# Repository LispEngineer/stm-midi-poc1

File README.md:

# MIDI Synthesizer Proof of Concept 1

**Feedback is very welcome!**

* Author: [Douglas P. Fields, Jr.](mailto:symbolics@lisp.engineer)
* My portions Copyright 2024 Douglas P. Fields, Jr.
* My portions License: Creative Commons Attribution-ShareAlike 4.0
  * AKA `CC BY-SA 4.0`
  * [See LICENSE.md](LICENSE.md) or [CC site](https://creativecommons.org/licenses/by-sa/4.0/deed.en)
* Started 2024-09-28
* Last updated 2025-04-20
* [Repo Self-Link](https://github.com/LispEngineer/stm-midi-poc1)

Overviews:
* 3D Views
  * 
  * 
* [Schematic PDF](stm-midi-poc1.pdf)
* [Board Plots as PDF](plots/stm-midi-poc1__Assembly.pdf)
  * From Board2PDF KiCAD Plugin
* [Interactive BOM](bom/ibom.html)
  * From Interactive BOM KiCAD Plugin

Design documents:
* [Design notes](Design.md)
* Designed in [KiCAD 8](https://www.kicad.org/)
* LCSC part numbers included for assembly by [JLCPCB](https://jlcpcb.com/)

Debuggers:
* Segger J-Link EDU Mini
* Segger J-Link Plus v10.1 (second hand)
  * Built in VCOM port - only seems to work at 115,200 baud
* ST-Link v3
* FTDI USB to TTL UART

Software:
* [Pinout](https://github.com/LispEngineer/stm-midi-poc1-sw)
* [STM Synth](https://github.com/LispEngineer/nucleo-uart)
* [My KiCAD Libraries](https://github.com/LispEngineer/KiCAD_Libraries)

Discussions:
* [Smaller Optoisolator](https://www.reddit.com/r/synthdiy/comments/1gghujj/smaller_midi_optoisolator/)

## Key Reference Documents

* [DS11853](TODO) - Datasheet: Arm® Cortex®-M7 32b MCU+FPU, 462DMIPS, up to 512KB Flash
  256+16+4KB RAM, USB OTG HS/FS, 18 TIMs, 3 ADCs, 21 com IF
* [RM0431](TODO) - STM32F72xxx ... advanced Arm®-based 32-bit MCUs
* [PM0253](TODO) - STM32F7 Series ... Cortex®-M7 processor programming manual
* [ES0360](TODO) - STM32F72xxx ... device limitations
* [AN2867](TODO) - Guidelines for oscillator design on ... STM32 MCUs/MPUs
* [AN4661](TODO) - Getting started with STM32F7 Series MCU hardware development
* [AN5612](TODO) - ESD protection of STM32 MCUs
* [AN4879](TODO) - Introduction to USB hardware and PCB guidelines using STM32 MCUs
* [AN4989](TODO) - STM32 microcontroller debug toolbox
* [AN4676](TODO) - STM32F7 Series peripheral interconnections
* [AN4031](TODO) - Using the STM32F2, STM32F4 and STM32F7 Series DMA controller

Moving to STM32H7:
* [AN5293](TODO) - Migration guide from STM32F7 Series to STMH74x/75x, STM32H72x/73x and STMH7A3/7Bx devices
* [AN4936](TODO) - Migration of microcontroller applications from STM32F7 Series to STM32H743/753 line

# Production Runs

I have been using JLCPCB.

* [JLCPCB instructions](https://jlcpcb.com/help/article/how-to-generate-gerber-and-drill-files-in-kicad-8)
  on creating Gerber and Drill files for KiCAD 8.
* You can also use the
  [JLCPCB KiCAD plugin](https://github.com/Bouni/kicad-jlcpcb-tools).
  * Installed using the *Plugin and Content Manager* in KiCAD.
  * This usefully shows you the stock count for your parts, and whether
    they are Basic or Extended.
  * Current version (2024-12-21) gives a lot of errors about redundant
    parts already in the catalog though (annoying).
* Or maybe I was using [this JLCPCB KiCAD plugin](https://github.com/bennymeg/Fabrication-Toolkit).

## Run 1 - EVT#1

* Submitted: 2024-10-27
* Git Commit: `6f9e281abe9c22ef3b995376c3df42217fc04524`
* Producer: JLCPCB
  * Order #W202410271206812 
* Boards: 5
* Assemblies: 2
* [BOM](jlcpcb/production_files/BOM-stm-midi-poc1.csv)
* [CPL](jlcpcb/production_files/CPL-stm-midi-poc1.csv)
* [Gerbers](jlcpcb/production_files/GERBER-stm-midi-poc1.zip)
* JLCPCB Corrected Part Placement
  
* [JLCPCB Submission](jlcpcb-production/run1-20241027/stm-midi-poc1 6f9e281abe9c22ef3b995376c3df42217fc04524_Y2.zip)
* Status: Production complete; in DHL's hands for delivery Nov 8
* Cost:
  * PCB: $28.02
  * Assembly: $79.66
  * Shipping: $32.60 (DHL)
  * Sales tax: $11.22
  * Total: $151.50

I received two fully populated boards. One was missing the J5 header.

## Run 2 - EVT#2

* Submitted: 2024-12-21 (11PM NYC time)
  * PCB and PCBA confirmed: 2024-12-22
* Git Commit: `e48a22093a1c81bb14c9082240e3d44837e7d75e`
* Producer: JLCPCB
* Order #W202412221204947 
* Boards: 5
* Assemblies: 2
* [BOM](jlcpcb/production_files/BOM-stm-midi-poc1.csv)
* [CPL](jlcpcb/production_files/CPL-stm-midi-poc1.csv)
* [Gerbers](jlcpcb/production_files/GERBER-stm-midi-poc1.zip)
* JLCPCB Corrected Part Placement
  
* [JLCPCB Submission](jlcpcb-production/run2-20241221/GERBER-stm-midi-poc1_Y3.zip)
* Status: Confirmed for PCB/PCBA
* Cost:
  * PCB: $8.00
  * Assembly: $86.40
  * Shipping: $58.36 (FedEx - "remote area" charge)
  * Sales tax: $12.22
  * Total: $164.98
* Received: 2025-01-03 (delivered on 2025-01-02)

Results:
* They did not add assembly holes this time (interesting, maybe re-used the mounting holes)
* STM32 Debugger (ST-Link v3) does not seem to reliably connect anymore.
  * It did allow me to download the firmware but is not reliable.
  * Sometimes it says "Failed to enable Live Expressions"
* SPI display works
* Audio Gain pins work
* Audio mute works
* Headphone output works
* Buttons & LEDs work

TODO:
* Test MIDI in/out
* Test Line out
* Test various resistors for the headphone
* Test I2C
* Test GPIO

# Miscellaneous Notes

* Footprints, models, etc., by their respective authors
* Some footprints, schematics, models are from these sources:
  * [Component Search Engine](https://componentsearchengine.com)
  * [Snap EDA](https://snapeda.com)
  * [EasyEDA](https://easyeda.com)
* Useful tools:
  * [EasyEDA2KiCAD](https://github.com/uPesy/easyeda2kicad.py)
  * [JLC Parts Finder](https://yaqwsx.github.io/jlcparts/)
  * [Altium Viewer](https://www.altium365.com/viewer/)
    * If you have Altium files and want to get details out of them
      but only use KiCAD

# KiCAD Configuration Notes

Using EasyEDA2KiCAD:

* Create a Path Substitution
  * Use main KiCAD window: Prefernces -> Configure Paths...
  * `EASYEDA2KICAD`
  * [Git Repository](https://github.com/LispEngineer/KiCAD_Libraries)
* Create a Footprint Library
  * `easyeda2kicad` Nickname
  * `${EASYEDA2KICAD}/easyeda2kicad.pretty`
* Create a Symbol Library
  * `easyeda2kicad` Nickname
  * `${EASYEDA2KICAD}/easyeda2kicad.kicad_sym` Library Path

# Status

* Schematic: Done
* LCSC part IDs: Almost Done
  * Need non-Red LEDs
* Schematic symbols: Done
* Footprints: Done
* 3D models: Done
* PCB Layout: Done
* Production 1 run: Done - in shipping

## TODOs

* Use STDC14 connector for ST-Link v3
  * Digikey [1175-1632-ND](https://www.digikey.com/en/products/detail/cnc-tech/3220-14-0300-00/3883270?s=N4IgTCBcDaIIxwOwFYC0cBsBmMqByAIgAQgC6AvkA)
    * Not in JLCPCB
  * Mouser [SHF-107-01-L-D-SM](https://www.mouser.com/ProductDetail/Samtec/SHF-107-01-L-D-SM?qs=%252BZP6%2F%252BtExtBY5XT826bN4g%3D%3D)
    * [Footprint](https://kinetictest.samtec.com/partnumber/shf-107-01-l-d-sm#featureinformation)
    * [JLCPCB C17640678](https://jlcpcb.com/partdetail/Samtec-SHF_107_01_L_DSM/C17640678) - $2???
    * [LCSC Alternative 1](https://www.lcsc.com/product-detail/Pin-Headers_Hanbo-Electronic-Hanbo-Electronic-HB-PH9-12727PB2GOB_C6332251.html) C6332251
    * [LCSC Alternative 2](https://www.lcsc.com/product-detail/Pin-Headers_HCTL-HCTL-PZ127-2-07-S_C3975190.html) C3975190 - 11¢
    * [LCSC Alternative 3](https://www.lcsc.com/product-detail/Pin-Headers_XKB-Connection-XKB-Connection-X1321WVS-2x07J-C40D53_C2881912.html) C2881912
* Use a 4-pin 32kHz clock?
* RN1 footprint and 3D model look a little bit off - footprint is a bit too small?
* Test points/pins
* MCU Pin 24 is not used - it is I2S1_MCK
* Incorporate my own ST-Link?
  * [See Hackaday](https://hackaday.io/project/179054-custom-st-link-v20-v21-v30)

### DONE

* DONE(EVT2): Find a much smaller Opto-isolator for MIDI than the one chosen here
  * [TLP2362](https://toshiba.semicon-storage.com/us/semiconductor/product/isolators-solid-state-relays/detail.TLP2362.html)
    is used by [Ksoloti 0.6](https://ksoloti.github.io/5-resources.html). Tested to work with
    1.8kΩ pull-up resistor instead of the schematic's 2.7kΩ.
    (Also worked with no pull-up resistor!)

# Board Layout Notes

4-layer design with Signal/GND/GND/Signal for EVT board.

Will do most important routing first on the top copper layer:
* Decoupling/bypass capacitors
* Clock signals
* High speed signals
  * USB
  * DAC
  * SWD

Remaining signals will be routed using "Manhattan routing."
That is, one signal layer will run up/down, the other will
run left/right, mostly.
* Top layer: up/down
* Bottom layer: left/right

After that, do these routings:
* Audio signals
* MIDI signals
* SPI
* I²C
* UI (Buttons, LEDs)
* GPIO
* Power

Fill in some positive power areas with fill.

Finally, the signal layers will be filled with GND at the end,
and the ground planes should be stitched together with lots
of vias.

## After Layout Is Done

* DRC check
* Cleanup Tracks & Vias

# BOM Notes

* Docs say you need a 4.7 uF ceramic capacitor with low ESR DS11853 Rev 9 page 105
  * Samsung CL10A475KO8NNNC works *but* Datasheet doesn't say what the ESR is, just "low ESR"
  * [Notes on the Cap](https://community.st.com/t5/stm32-mcus-products/how-supply-stm32f446ret6/td-p/635424)

* [ISOM8710](https://www.ti.com/product/ISOM8710) 
  is a drop-in replacement for the
  [TLP2362](https://toshiba.semicon-storage.com/us/semiconductor/product/isolators-solid-state-relays/detail.TLP2362.html)
  * Same form factor
  * Same functionality (tested on a breadboard)
  * Same circuit
  * Does not seem to be carried at JLCPCB

# Notes for future

* Use fewer header types, they're all extended parts
* Don't use the Resistor Network - due to the Extended parts fee from JLC
  * OTOH there are no 56Ω resistors in the Basic parts library
  * C25127 is an extended part 0402
  * C17714 is an 0805 47Ω
* Add I/O activity LEDs for MIDI & serial?
* Add a pin for VBUS (5V from USB) and USB GND
* Add pins for the TRS jacks
* Get a 4-way switch for gain?
* Rewrire the headphone amp like Pimoroni?
* Move console from UART3 to UART2
  * Move console pins next to SWD pins for easy use with STLink
* Install UART to USB bridge
  * [FTDI FT234XD](https://ftdichip.com/products/ft234xd/) is a nice 12-pin package
  * [Example Circuit](https://github.com/z4yx/USB-C-Serial)
  * [JLCPCB Part](https://jlcpcb.com/partdetail/Ftdi-FT234XDR/C132158)

Longer term
* Move to an STM32H7 device
* Move to a [higher pin-count device](https://www.st.com/en/microcontrollers-microprocessors/stm32h7-series/products.html)
  * LQFP 64, 100, 144, 176, 208
    * low-profile quad flat package - LQFP 64 currently in use
  * TFBGA 216, 225, 240+25
    * Thin Profile Fine Pitch Ball Grid Array
    * thinner than other BGA packages - Gemini
  * UFBGA 144, 169, 176+25
    * ultra fine pitch ball grid array
  * VFQFPN 68
    * thermally enhanced very thin profile fine pitch quad flat package no lead (Gemini)
  * WLCSP 132, 156
    * [Wafer-Level Chip Scale Packaging](https://www.flashpcb.com/blog/QFP-QFN-BGA-WLSCP)
* Add an SDRAM

# EasyEDA 2 KiCAD Notes

`python -m easyeda2kicad --full --lcsc_id=Cxxxxx`

[My imported library is in GitHub](https://github.com/LispEngineer/KiCAD_Libraries).

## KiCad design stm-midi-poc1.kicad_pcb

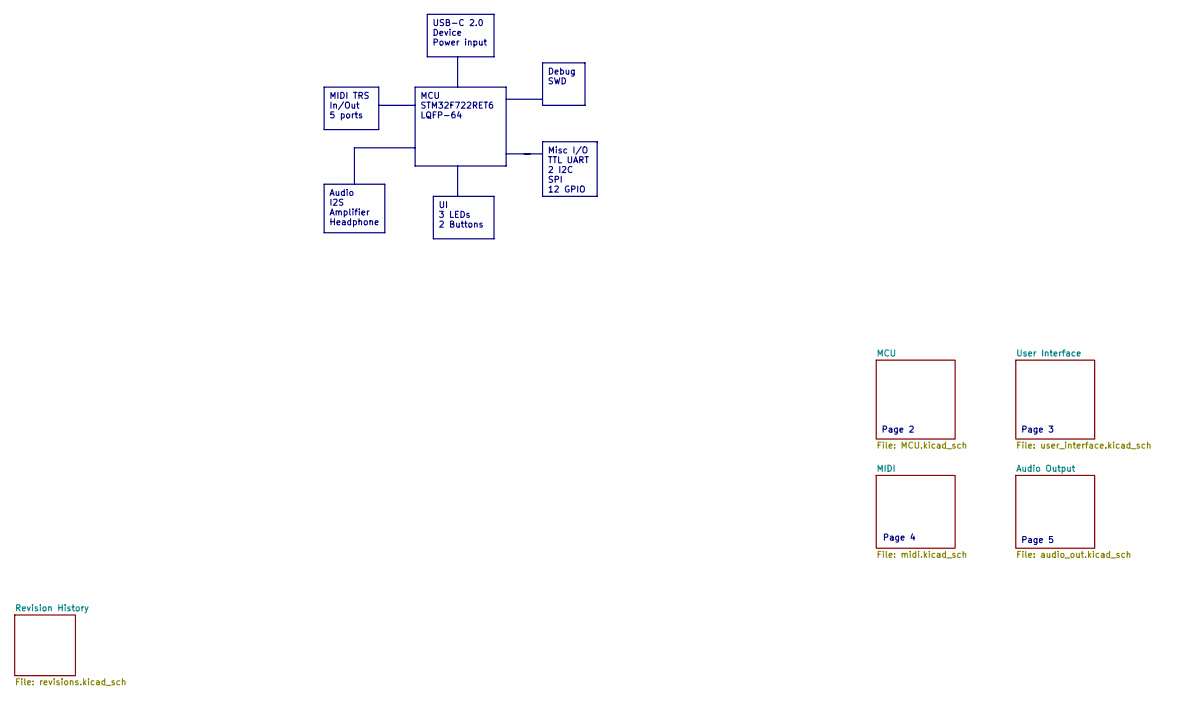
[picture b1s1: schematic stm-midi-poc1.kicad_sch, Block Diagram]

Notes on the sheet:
MIDI TRS In/Out 5 ports
Misc I/O TTL UART 2 I2C SPI 12 GPIO
MCU STM32F722RET6 LQFP-64
UI 3 LEDs 2 Buttons
USB-C 2.0 Device Power input
Audio I2S Amplifier Headphone
Debug SWD
Page 5
Page 3
Page 2
Page 4

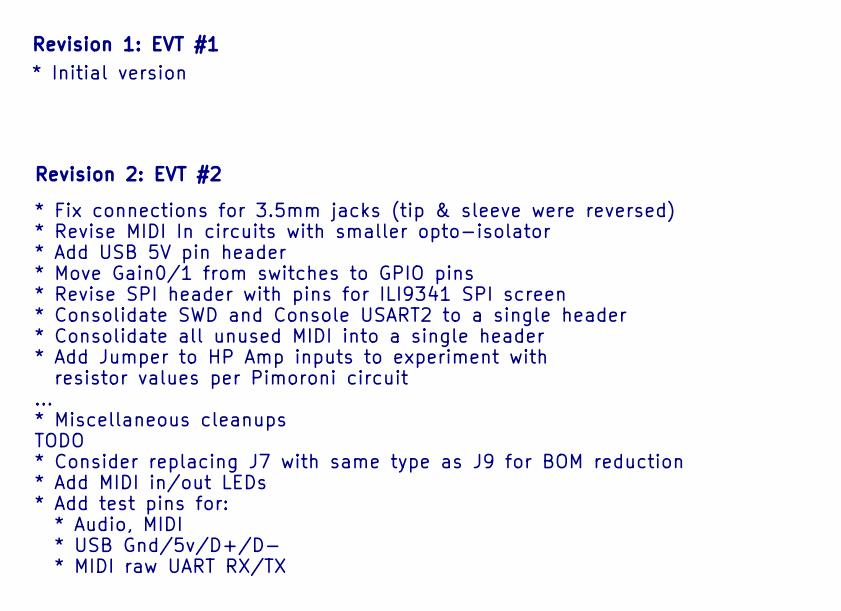
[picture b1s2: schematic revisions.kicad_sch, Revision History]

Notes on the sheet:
Revision 1: EVT #1
* Fix connections for 3.5mm jacks (tip & sleeve were reversed) * Revise MIDI In circuits with smaller opto-isolator * Add USB 5V pin header * Move Gain0/1 from switches to GPIO pins * Revise SPI header with pins for ILI9341 SPI screen * Consolidate SWD and Console USART2 to a single header * Consol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
Revision 2: EVT #2
* Initial version

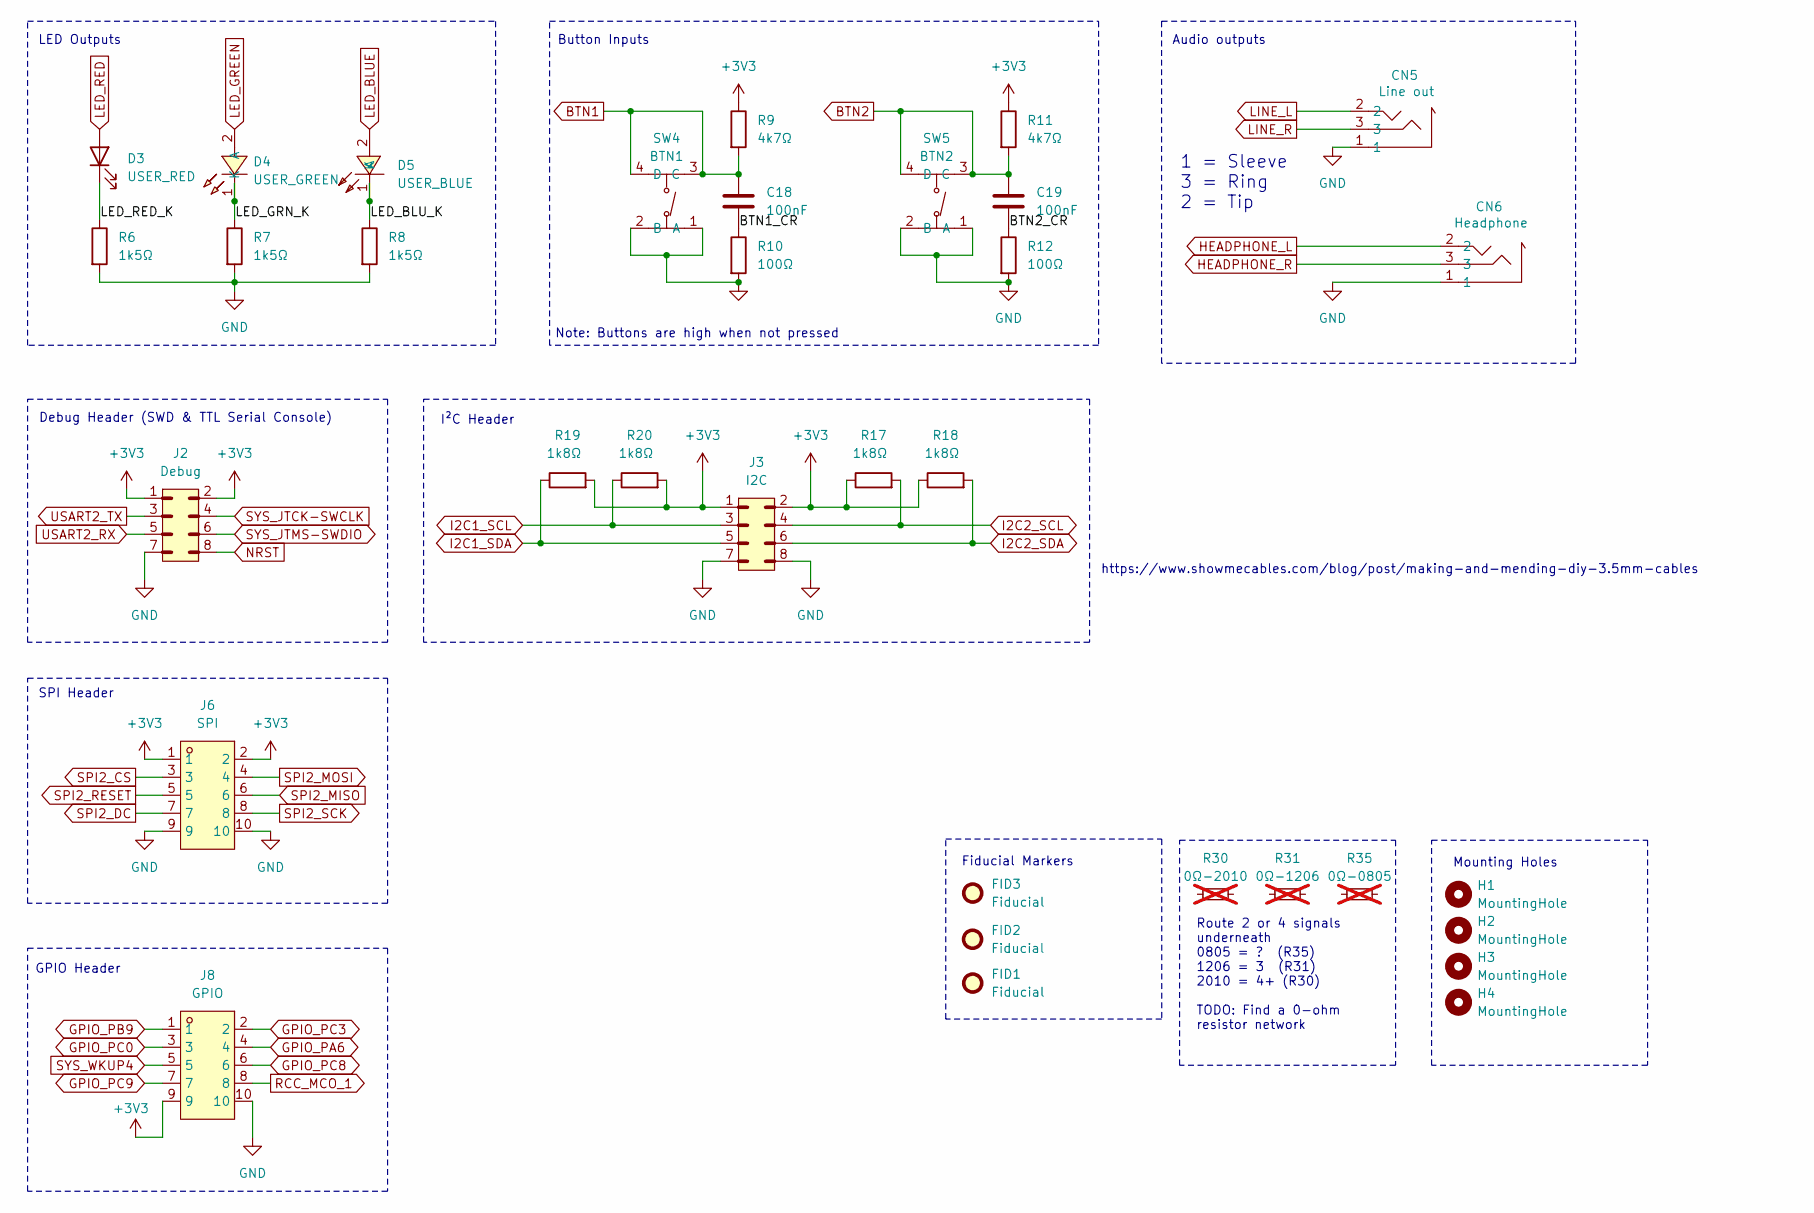
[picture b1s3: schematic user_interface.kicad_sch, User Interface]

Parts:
C18, C19: 100nF; C_0402_1005Metric; Manu Part CL05B104KB54PNC; LCSC C307331
CN5: Line out; AUDIO-SMD_PJ-321A-4A; Manu Part PJ-321A-4A; LCSC Part C879743
CN6: Headphone; AUDIO-SMD_PJ-321A-4A; Manu Part PJ-321A-4A; LCSC Part C879743
D3: USER_RED; LED_0603_1608Metric; Manu Part KT-0603R; LCSC C2286
D4: USER_GREEN; LED0603-RD; LCSC Part C19189745
D5: USER_BLUE; LED0603-RD; LCSC Part C2288
FID1, FID2, FID3: Fiducial; Fiducial_1mm_Mask2mm
H1, H2, H3, H4: MountingHole; MountingHole_2.2mm_M2
J2: Debug; PinHeader_2x04_P2.54mm_Vertical; Manu Part PZ2.54-2*4; LCSC C5156676
J3: I2C; PinHeader_2x04_P2.54mm_Vertical; Manu Part PZ2.54-2*4; LCSC C5156676
J6: SPI; HDR-TH_10P-P2.54-V-M-R2-C5-S2.54-1; LCSC Part C5156677
J8: GPIO; HDR-TH_10P-P2.54-V-M-R2-C5-S2.54-1; LCSC Part C5156677
R6, R7, R8: 1k5Ω; R_0402_1005Metric; Manu Part 0402WGF1501TCE; LCSC C25867
R9, R11: 4k7Ω; R_0402_1005Metric; Manu Part 0402WGF4701TCE; LCSC C25900
R10, R12: 100Ω; R_0402_1005Metric; Manu Part 0402WGF1000TCE; LCSC C25076
R17, R18, R19, R20: 1k8Ω; R_0402_1005Metric; Manu Part 0402WGF1801TCE; LCSC C25871
R30: 0Ω-2010; R_2010_5025Metric; Manu Part AC2010JK-070RL; LCSC C144433; not fitted
R31: 0Ω-1206; R_1206_3216Metric; Manu Part 1206W4F0000T5E; LCSC C17888; not fitted
R35: 0Ω-0805; R_0805_2012Metric; Manu Part 0805W8F0000T5E; LCSC C17477; not fitted
SW4: BTN1; SW-SMD_4P-L5.1-W5.1-P3.70-LS6.5-TL-2; Manu Part TS-1187A-B-A-B; LCSC Part C318884
SW5: BTN2; SW-SMD_4P-L5.1-W5.1-P3.70-LS6.5-TL-2; Manu Part TS-1187A-B-A-B; LCSC Part C318884

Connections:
+3V3: J2.1, J2.2, J3.1, J3.2, J6.1, J6.2, J8.9, R9.1, R11.1, R17.1, R18.1, R19.2, R20.2; also elsewhere on the board
/User Interface/BTN1_CR: C18.2, R10.1
/User Interface/BTN2_CR: C19.2, R12.1
/User Interface/LED_BLU_K: D5.1 (K), R8.1
/User Interface/LED_GRN_K: D4.1 (K), R7.1
/User Interface/LED_RED_K: D3.1 (K), R6.1
BTN1: C18.1, R9.2, SW4.3 (C), SW4.4 (D); also elsewhere on the board
BTN2: C19.1, R11.2, SW5.3 (C), SW5.4 (D); also elsewhere on the board
GND: CN5.1, CN6.1, J2.7, J3.7, J3.8, J6.9, J6.10, J8.10, R6.2, R7.2, R8.2, R10.2, R12.2, SW4.1 (A), SW4.2 (B), SW5.1 (A), SW5.2 (B); also elsewhere on the board
GPIO_PA6: J8.4; also elsewhere on the board
GPIO_PB9: J8.1; also elsewhere on the board
GPIO_PC0: J8.3; also elsewhere on the board
GPIO_PC3: J8.2; also elsewhere on the board
GPIO_PC8: J8.6; also elsewhere on the board
GPIO_PC9: J8.7; also elsewhere on the board
HEADPHONE_L: CN6.2; also elsewhere on the board
HEADPHONE_R: CN6.3; also elsewhere on the board
I2C1_SCL: J3.3, R20.1; also elsewhere on the board
I2C1_SDA: J3.5, R19.1; also elsewhere on the board
I2C2_SCL: J3.4, R17.2; also elsewhere on the board
I2C2_SDA: J3.6, R18.2; also elsewhere on the board
LED_BLUE: D5.2 (A); also elsewhere on the board
LED_GREEN: D4.2 (A); also elsewhere on the board
LED_RED: D3.2 (A); also elsewhere on the board
LINE_L: CN5.2; also elsewhere on the board
LINE_R: CN5.3; also elsewhere on the board
NRST: J2.8; also elsewhere on the board
RCC_MCO_1: J8.8; also elsewhere on the board
SPI2_CS: J6.3; also elsewhere on the board
SPI2_DC: J6.7; also elsewhere on the board
SPI2_MISO: J6.6; also elsewhere on the board
SPI2_MOSI: J6.4; also elsewhere on the board
SPI2_RESET: J6.5; also elsewhere on the board
SPI2_SCK: J6.8; also elsewhere on the board
SYS_JTCK-SWCLK: J2.4; also elsewhere on the board
SYS_JTMS-SWDIO: J2.6; also elsewhere on the board
SYS_WKUP4: J8.5; also elsewhere on the board
USART2_RX: J2.5; also elsewhere on the board
USART2_TX: J2.3; also elsewhere on the board

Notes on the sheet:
Mounting Holes
SPI Header
Debug Header (SWD & TTL Serial Console)
1 = Sleeve 3 = Ring 2 = Tip
Note: Buttons are high when not pressed
Route 2 or 4 signals underneath 0805 = ? (R35) 1206 = 3 (R31) 2010 = 4+ (R30) TODO: Find a 0-ohm resistor network
Audio outputs
GPIO Header
I²C Header
LED Outputs
https://www.showmecables.com/blog/post/making-and-mending-diy-3.5mm-cables
Button Inputs
Fiducial Markers

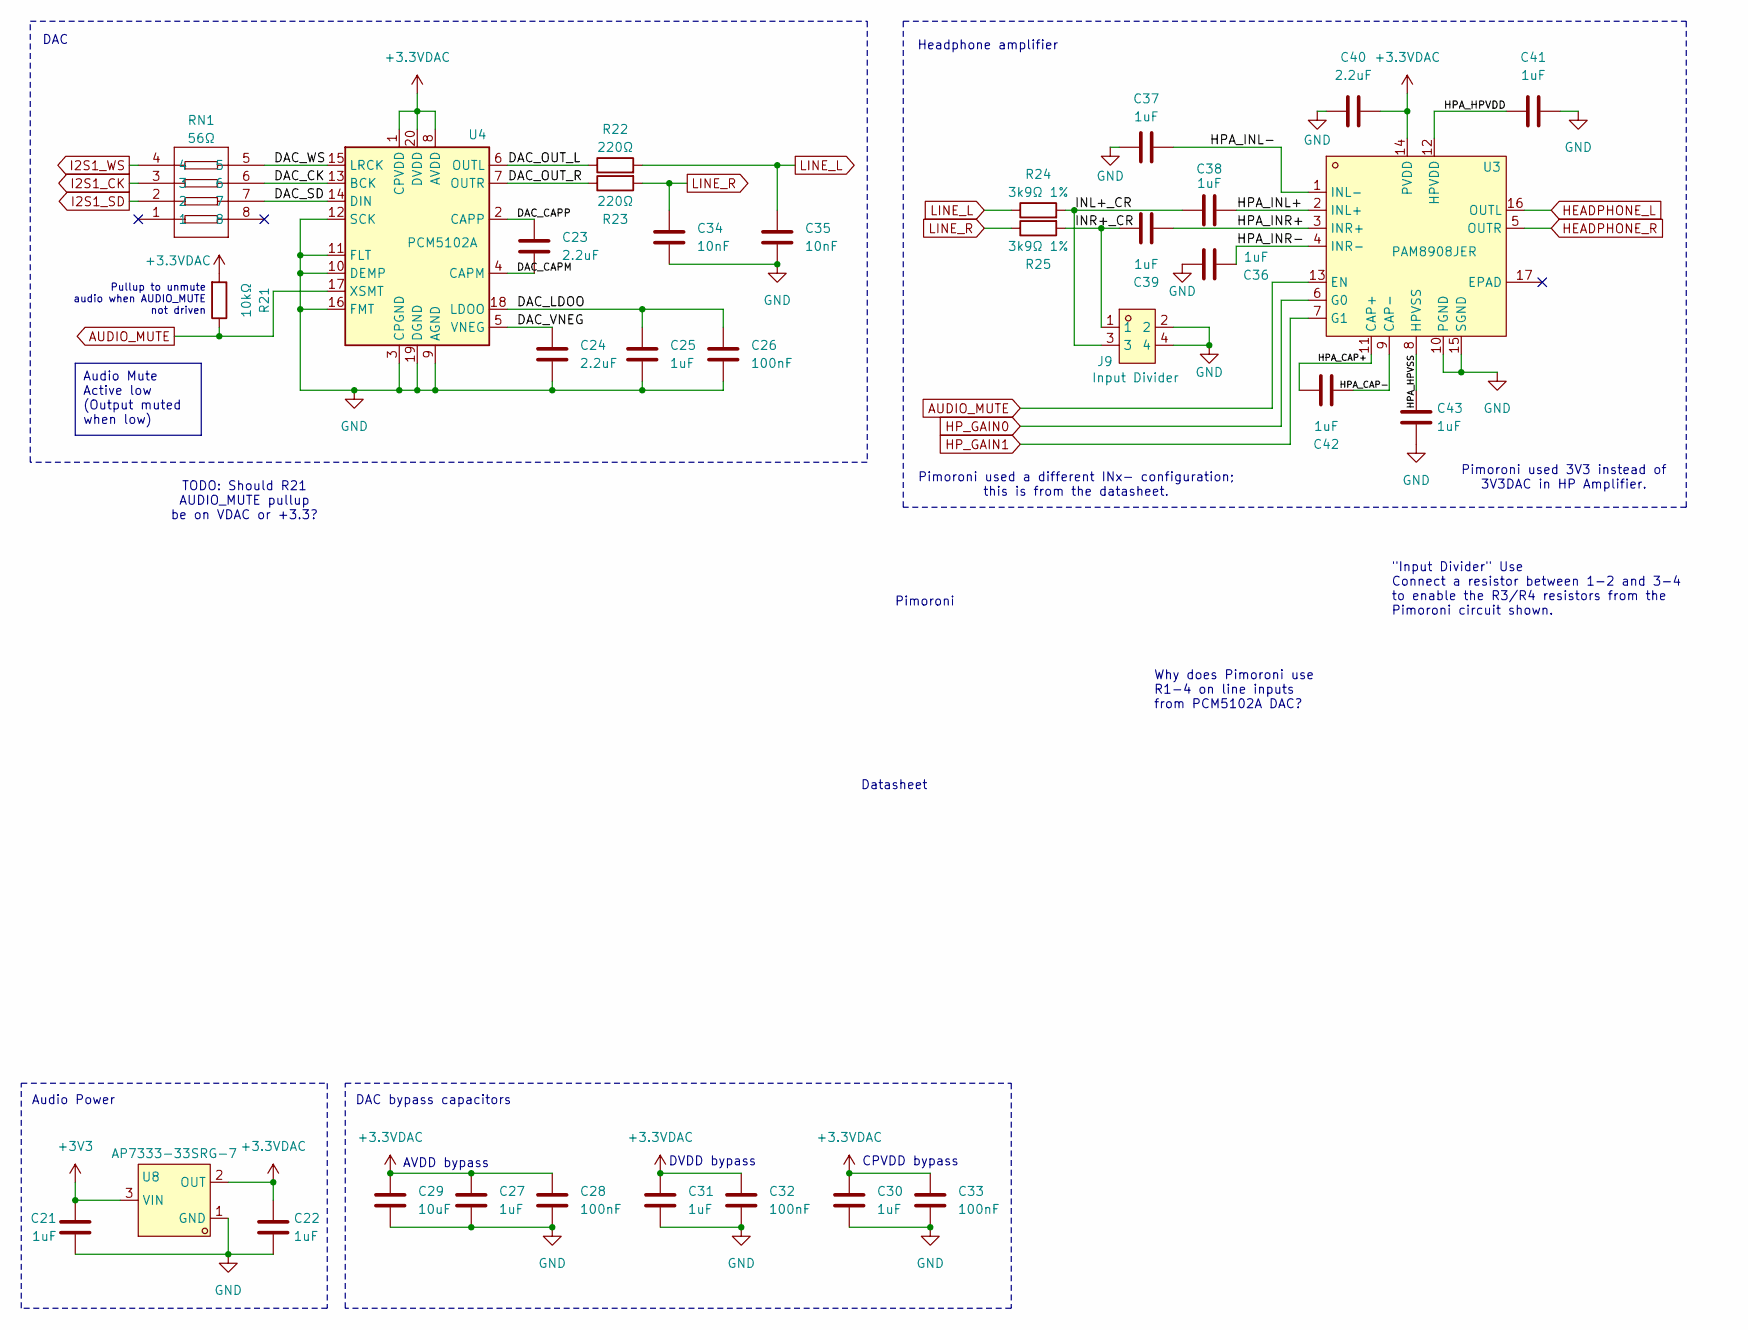
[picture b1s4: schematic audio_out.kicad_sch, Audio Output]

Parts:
C21, C22, C25, C27, C30, C31, C36, C37, C38, C39, C41, C42, C43: 1uF; C_0402_1005Metric; Manu Part CL05A105KA5NQNC; LCSC C52923
C23, C24, C40: 2.2uF; C_0805_2012Metric; Manu Part CL21A225KBQNNNE; LCSC C377773
C26, C28, C32, C33: 100nF; C_0402_1005Metric; Manu Part CL05B104KB54PNC; LCSC C307331
C29: 10uF; C_0603_1608Metric; Manu Part CL10A106MA8NRNC; LCSC C96446
C34, C35: 10nF; C_0402_1005Metric; Manu Part CL05B103KB5NNNC; LCSC C15195
J9: Input Divider; HDR-TH_4P-P2.54-V-F-R2-C2-S2.54; LCSC Part C2977590
R21: 10kΩ; R_0402_1005Metric; Manu Part 0402WGF1002TCE; LCSC C25744
R22, R23: 220Ω; R_0402_1005Metric; Manu Part 0402WGF2200TCE; LCSC C25091
R24, R25: 3k9Ω 1%; R_0402_1005Metric; Manu Part 0402WGF3901TCE; LCSC C51721
RN1: 56Ω; RES-ARRAY-SMD_0603-8P-L3.2-W1.6-BL; Manu Part 4D03WGJ0560T5E; LCSC Part C25512
U3: PAM8908JER; QFN-16_L3.0-W3.0-P0.50-BL-EP1.7; Manu Part PAM8908JER; LCSC Part C33233
U4: PCM5102A; TSSOP-20_4.4x6.5mm_P0.65mm; Manu Part PCM5102APWR; LCSC C107671
U8: AP7333-33SRG-7; SOT-23-3_L2.9-W1.3-P1.90-LS2.4-BR; Manu Part AP7333-33SRG-7; LCSC Part C150745

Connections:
+3.3VDAC: C22.1, C27.1, C28.1, C29.1, C30.1, C31.1, C32.1, C33.1, C40.2, R21.2, U3.14 (PVDD), U4.1 (CPVDD), U4.8 (AVDD), U4.20 (DVDD), U8.2 (OUT)
+3V3: C21.1, U8.3 (VIN); also elsewhere on the board
/Audio Output/DAC_CAPM: C23.2, U4.4 (CAPM)
/Audio Output/DAC_CAPP: C23.1, U4.2 (CAPP)
/Audio Output/DAC_CK: RN1.6, U4.13 (BCK)
/Audio Output/DAC_LDOO: C25.1, C26.1, U4.18 (LDOO)
/Audio Output/DAC_OUT_L: R22.1, U4.6 (OUTL)
/Audio Output/DAC_OUT_R: R23.1, U4.7 (OUTR)
/Audio Output/DAC_SD: RN1.7, U4.14 (DIN)
/Audio Output/DAC_VNEG: C24.1, U4.5 (VNEG)
/Audio Output/DAC_WS: RN1.5, U4.15 (LRCK)
/Audio Output/HPA_CAP+: C42.2, U3.11 (CAP+)
/Audio Output/HPA_CAP-: C42.1, U3.9 (CAP-)
/Audio Output/HPA_HPVDD: C41.1, U3.12 (HPVDD)
/Audio Output/HPA_HPVSS: C43.1, U3.8 (HPVSS)
/Audio Output/HPA_INL+: C38.2, U3.2 (INL+)
/Audio Output/HPA_INL-: C37.2, U3.1 (INL-)
/Audio Output/HPA_INR+: C39.2, U3.3 (INR+)
/Audio Output/HPA_INR-: C36.2, U3.4 (INR-)
AUDIO_MUTE: R21.1, U3.13 (EN), U4.17 (XSMT); also elsewhere on the board
GND: C21.2, C22.2, C24.2, C25.2, C26.2, C27.2, C28.2, C29.2, C30.2, C31.2, C32.2, C33.2, C34.2, C35.2, C36.1, C37.1, C40.1, C41.2, C43.2, J9.2, J9.4, U3.10 (PGND), U3.15 (SGND), U4.3 (CPGND), U4.9 (AGND), U4.10 (DEMP), U4.11 (FLT), U4.12 (SCK), U4.16 (FMT), U4.19 (DGND), U8.1 (GND); also elsewhere on the board
HEADPHONE_L: U3.16 (OUTL); also elsewhere on the board
HEADPHONE_R: U3.5 (OUTR); also elsewhere on the board
HP_GAIN0: U3.6 (G0); also elsewhere on the board
HP_GAIN1: U3.7 (G1); also elsewhere on the board
I2S1_CK: RN1.3; also elsewhere on the board
I2S1_SD: RN1.2; also elsewhere on the board
I2S1_WS: RN1.4; also elsewhere on the board
LINE_L: C35.1, R22.2, R24.1; also elsewhere on the board
LINE_R: C34.1, R23.2, R25.1; also elsewhere on the board

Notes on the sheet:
Audio Mute Active low (Output muted when low)
Pimoroni used 3V3 instead of 3V3DAC in HP Amplifier.
DVDD bypass
Headphone amplifier
TODO: Should R21 AUDIO_MUTE pullup be on VDAC or +3.3?
Pullup to unmute audio when AUDIO_MUTE not driven
DAC bypass capacitors
CPVDD bypass
Pimoroni
Datasheet
AVDD bypass
Why does Pimoroni use R1-4 on line inputs from PCM5102A DAC?
Audio Power
"Input Divider" Use Connect a resistor between 1-2 and 3-4 to enable the R3/R4 resistors from the Pimoroni circuit shown.
Pimoroni used a different INx- configuration; this is from the datasheet.
DAC

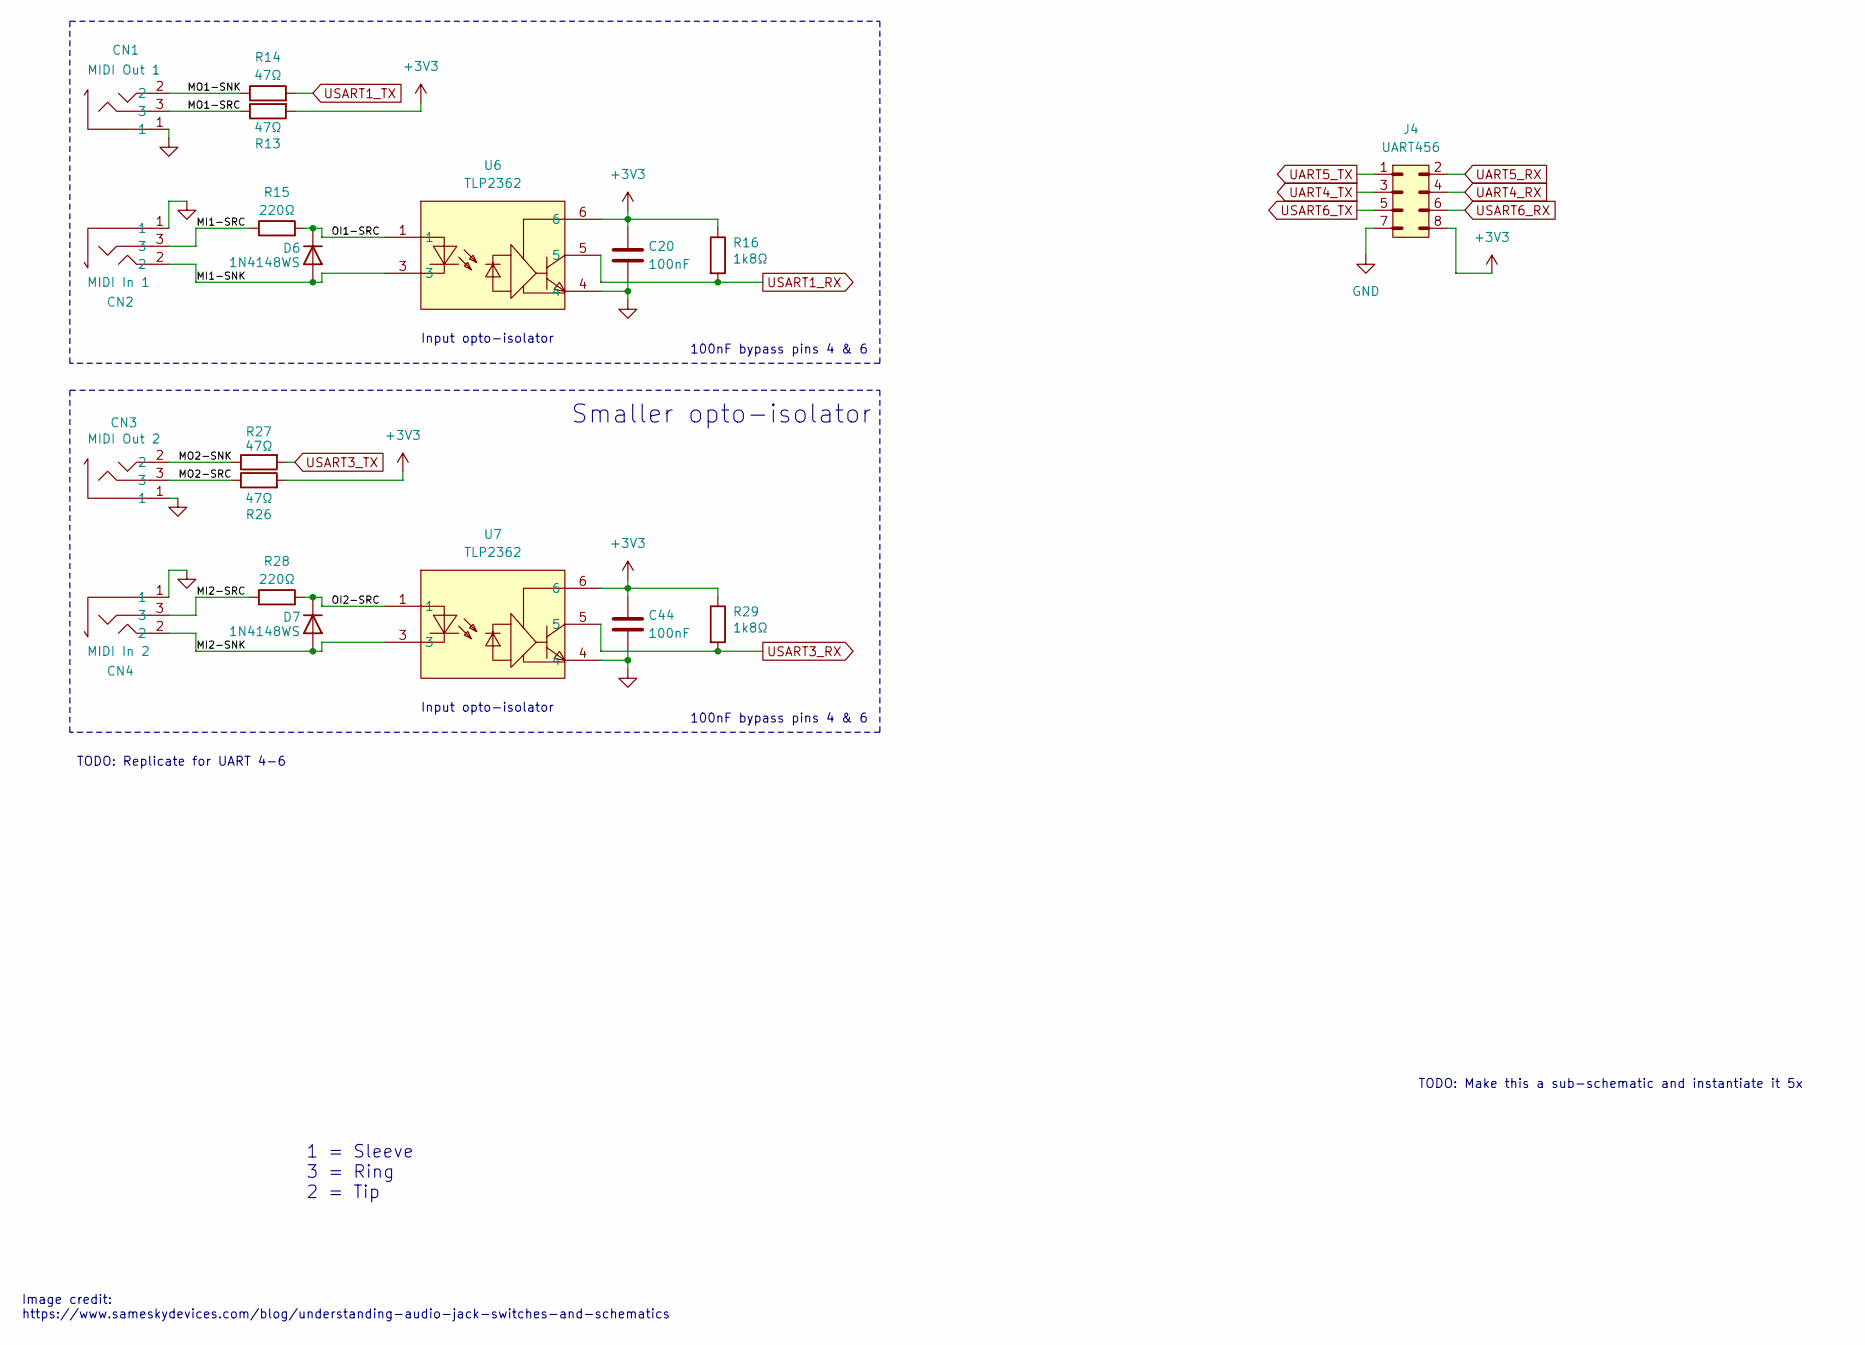
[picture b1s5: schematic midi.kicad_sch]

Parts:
C20, C44: 100nF; C_0402_1005Metric; Manu Part CL05B104KB54PNC; LCSC C307331
CN1: MIDI Out 1; AUDIO-SMD_PJ-321A-4A; Manu Part PJ-321A-4A; LCSC Part C879743
CN2: MIDI In 1; AUDIO-SMD_PJ-321A-4A; Manu Part PJ-321A-4A; LCSC Part C879743
CN3: MIDI Out 2; AUDIO-SMD_PJ-321A-4A; Manu Part PJ-321A-4A; LCSC Part C879743
CN4: MIDI In 2; AUDIO-SMD_PJ-321A-4A; Manu Part PJ-321A-4A; LCSC Part C879743
D6, D7: 1N4148WS; D_SOD-323; LCSC C2128
J4: UART456; PinHeader_2x04_P2.54mm_Vertical; Manu Part PZ2.54-2*4; LCSC C5156676
R13, R14, R26, R27: 47Ω; R_0402_1005Metric; Manu Part 0402WGF470JTCE; LCSC C25118
R15, R28: 220Ω; R_0402_1005Metric; Manu Part 0402WGF2200TCE; LCSC C25091
R16, R29: 1k8Ω; R_0402_1005Metric; Manu Part 0402WGF1801TCE; LCSC C25871
U6, U7: TLP2362; OPTO-SMD-5_L3.7-W4.6-P1.27-LS7.0-BR; LCSC Part C37658

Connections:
+3V3: C20.1, C44.1, J4.8, R13.2, R16.1, R26.2, R29.1, U6.6, U7.6; also elsewhere on the board
/MIDI/MI1-SNK: CN2.2, D6.2 (A), U6.3
/MIDI/MI1-SRC: CN2.3, R15.1
/MIDI/MI2-SNK: CN4.2, D7.2 (A), U7.3
/MIDI/MI2-SRC: CN4.3, R28.1
/MIDI/MO1-SNK: CN1.2, R14.1
/MIDI/MO1-SRC: CN1.3, R13.1
/MIDI/MO2-SNK: CN3.2, R27.1
/MIDI/MO2-SRC: CN3.3, R26.1
/MIDI/OI1-SRC: D6.1 (K), R15.2, U6.1
/MIDI/OI2-SRC: D7.1 (K), R28.2, U7.1
GND: C20.2, C44.2, CN1.1, CN2.1, CN3.1, CN4.1, J4.7, U6.4, U7.4; also elsewhere on the board
UART4_RX: J4.4; also elsewhere on the board
UART4_TX: J4.3; also elsewhere on the board
UART5_RX: J4.2; also elsewhere on the board
UART5_TX: J4.1; also elsewhere on the board
USART1_RX: R16.2, U6.5; also elsewhere on the board
USART1_TX: R14.2; also elsewhere on the board
USART3_RX: R29.2, U7.5; also elsewhere on the board
USART3_TX: R27.2; also elsewhere on the board
USART6_RX: J4.6; also elsewhere on the board
USART6_TX: J4.5; also elsewhere on the board

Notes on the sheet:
Image credit: https://www.sameskydevices.com/blog/understanding-audio-jack-switches-and-schematics
TODO: Replicate for UART 4-6
Input opto-isolator
1 = Sleeve 3 = Ring 2 = Tip
Smaller opto-isolator
TODO: Make this a sub-schematic and instantiate it 5x
100nF bypass pins 4 & 6

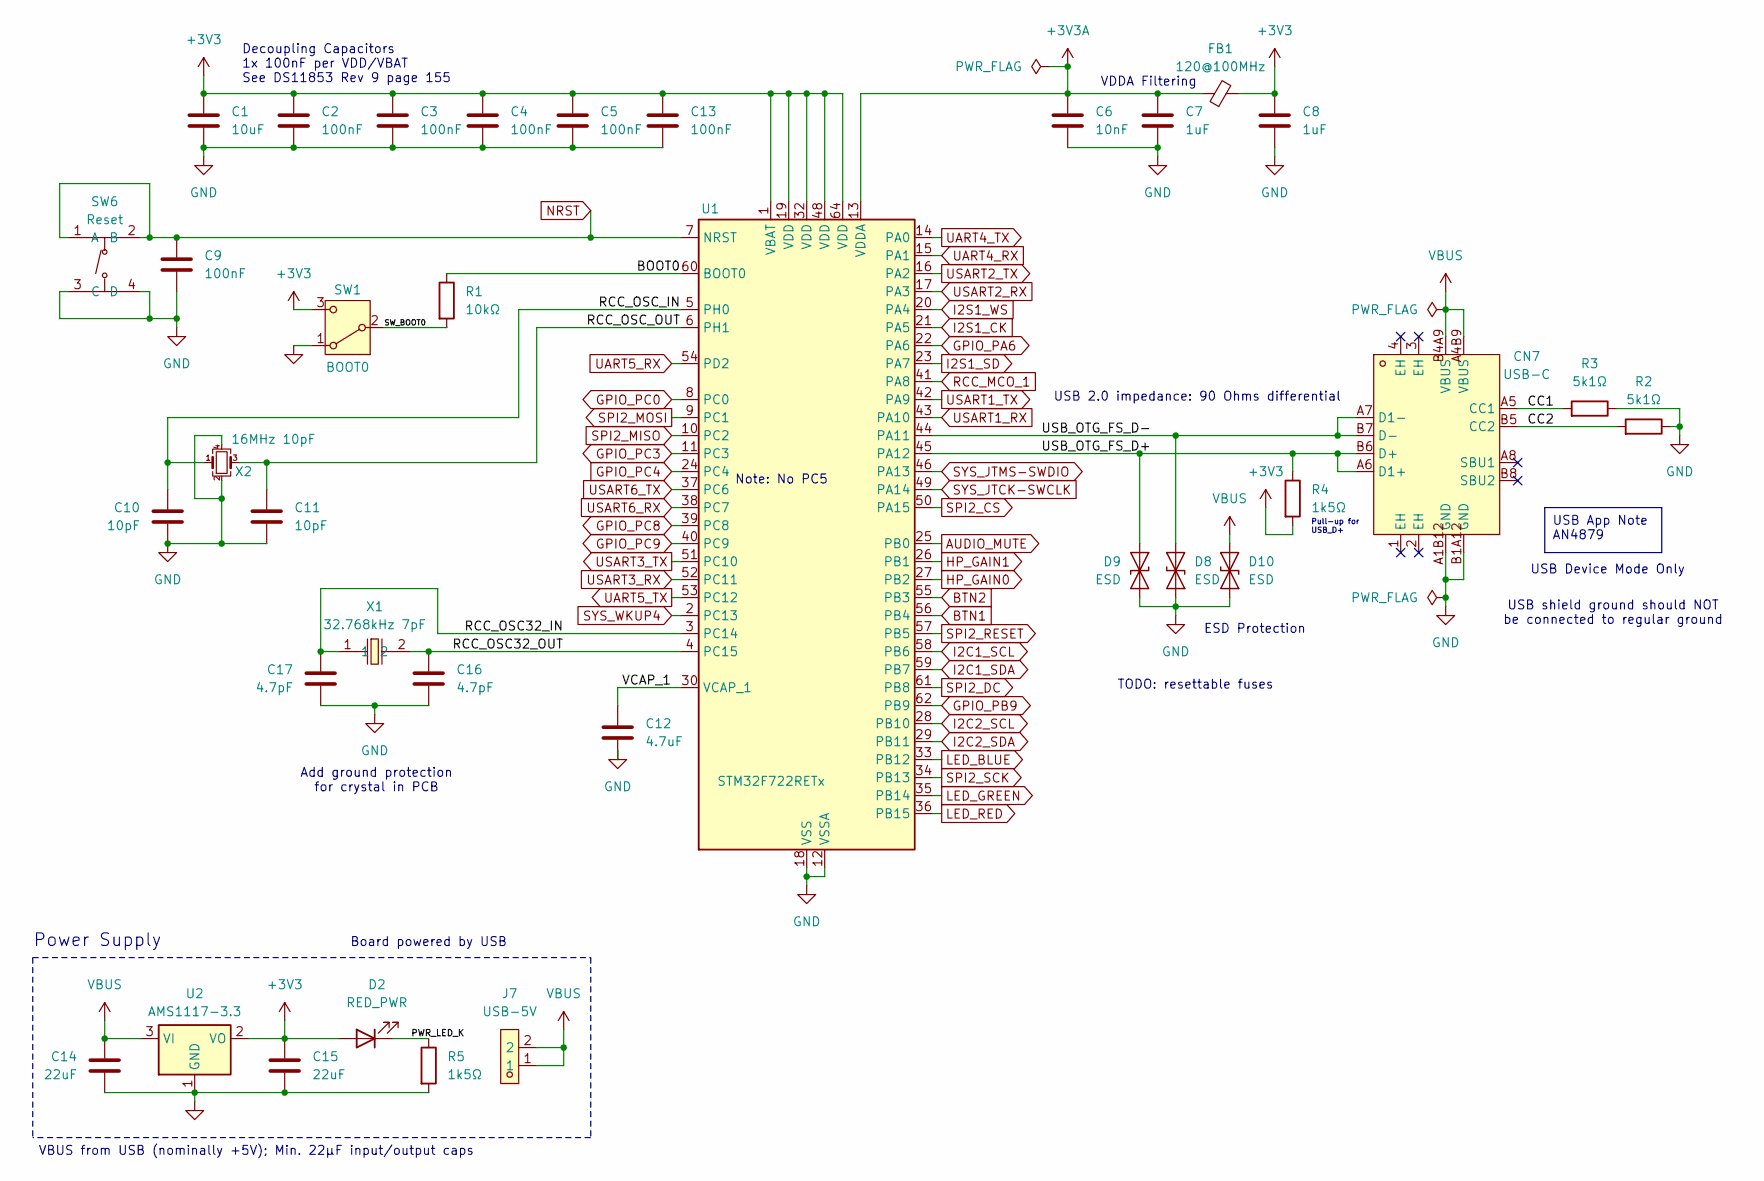
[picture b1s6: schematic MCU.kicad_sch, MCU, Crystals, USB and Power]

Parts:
C1: 10uF; C_0603_1608Metric; Manu Part CL10A106MA8NRNC; LCSC C96446
C2, C3, C4, C5, C9, C13: 100nF; C_0402_1005Metric; Manu Part CL05B104KB54PNC; LCSC C307331
C6: 10nF; C_0402_1005Metric; Manu Part CL05B103KB5NNNC; LCSC C15195
C7, C8: 1uF; C_0402_1005Metric; Manu Part CL05A105KA5NQNC; LCSC C52923
C10, C11: 10pF; C_0402_1005Metric; Manu Part CL05C100JB5NNNC; LCSC C32949
C12: 4.7uF; C_0603_1608Metric; Manu Part CL10A475KO8NNNC; LCSC C19666
C14, C15: 22uF; C_0805_2012Metric; Manu Part CL21A226MAQNNNE; LCSC C45783
C16, C17: 4.7pF; C_0402_1005Metric; Manu Part 0402CG4R7C500NT; LCSC C1569
CN7: USB-C; USB-C-SMD_GT-USB-7010I; Manu Part GT-USB-7010i; LCSC Part C5362630
D2: RED_PWR; LED_0603_1608Metric; Manu Part KT-0603R; LCSC C2286
D8, D9, D10: ESD; D_SOD-923; Manu Part ESD9B5.0ST5G; LCSC C111566
FB1: 120@100MHz; L_0603_1608Metric; Manu Part FCM1608KF-601T05; LCSC C133937
J7: USB-5V; HDR-TH_2P-P2.54-V-M-1; LCSC Part C5383111
R1: 10kΩ; R_0402_1005Metric; Manu Part 0402WGF1002TCE; LCSC C25744
R2, R3: 5k1Ω; R_0402_1005Metric; Manu Part 0402WGF5101TCE; LCSC C25905
R4, R5: 1k5Ω; R_0402_1005Metric; Manu Part 0402WGF1501TCE; LCSC C25867
SW1: BOOT0; SW_SPDT_PCM12; Manu Part SSSS811101; LCSC C109335
SW6: Reset; SW-SMD_4P-L5.1-W5.1-P3.70-LS6.5-TL-2; Manu Part TS-1187A-B-A-B; LCSC Part C318884
U1: STM32F722RETx; LQFP-64_10x10mm_P0.5mm; Manu Part STM32F722RET6; LCSC C118207
U2: AMS1117-3.3; SOT-223-3_TabPin2; Manu Part AMS1117-3.3; LCSC C6186
X1: 32.768kHz 7pF; FC-135R_L3.2-W1.5; Manu Part Q13FC13500002; LCSC Part C48615
X2: 16MHz 10pF; Crystal_SMD_3225-4Pin_3.2x2.5mm; Manu Part X322516MMB4SI; LCSC C112972

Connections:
+3V3: C1.1, C2.1, C3.1, C4.1, C5.1, C8.1, C13.1, C15.1, D2.2 (A), FB1.2, R4.2, SW1.3 (C), U1.1 (VBAT), U1.19 (VDD), U1.32 (VDD), U1.48 (VDD), U1.64 (VDD), U2.2 (VO); also elsewhere on the board
+3V3A: C6.1, C7.1, FB1.1, U1.13 (VDDA)
/MCU/BOOT0: R1.1, U1.60 (BOOT0)
/MCU/CC1: CN7.A5 (CC1), R3.2
/MCU/CC2: CN7.B5 (CC2), R2.2
/MCU/PWR_LED_K: D2.1 (K), R5.1
/MCU/RCC_OSC32_IN: C17.1, U1.3 (PC14), X1.1
/MCU/RCC_OSC32_OUT: C16.1, U1.4 (PC15), X1.2
/MCU/RCC_OSC_IN: C10.1, U1.5 (PH0), X2.1
/MCU/RCC_OSC_OUT: C11.1, U1.6 (PH1), X2.3
/MCU/SW_BOOT0: R1.2, SW1.2 (B)
/MCU/USB_OTG_FS_D+: CN7.A6 (D1+), CN7.B6 (D+), D9.2 (A2), R4.1, U1.45 (PA12)
/MCU/USB_OTG_FS_D-: CN7.A7 (D1-), CN7.B7 (D-), D8.2 (A2), U1.44 (PA11)
/MCU/VCAP_1: C12.1, U1.30 (VCAP_1)
AUDIO_MUTE: U1.25 (PB0); also elsewhere on the board
BTN1: U1.56 (PB4); also elsewhere on the board
BTN2: U1.55 (PB3); also elsewhere on the board
GND: C1.2, C2.2, C3.2, C4.2, C5.2, C6.2, C7.2, C8.2, C9.2, C10.2, C11.2, C12.2, C13.2, C14.2, C15.2, C16.2, C17.2, CN7.A1B12 (GND), CN7.B1A12 (GND), D8.1 (A1), D9.1 (A1), D10.1 (A1), R2.1, R3.1, R5.2, SW1.1 (A), SW6.3 (C), SW6.4 (D), U1.12 (VSSA), U1.18 (VSS), U1.31 (VSS), U1.47 (VSS), U1.63 (VSS), U2.1 (GND), X2.2, X2.4; also elsewhere on the board
GPIO_PA6: U1.22 (PA6); also elsewhere on the board
GPIO_PB9: U1.62 (PB9); also elsewhere on the board
GPIO_PC0: U1.8 (PC0); also elsewhere on the board
GPIO_PC3: U1.11 (PC3); also elsewhere on the board
GPIO_PC4: U1.24 (PC4)
GPIO_PC8: U1.39 (PC8); also elsewhere on the board
GPIO_PC9: U1.40 (PC9); also elsewhere on the board
HP_GAIN0: U1.27 (PB2); also elsewhere on the board
HP_GAIN1: U1.26 (PB1); also elsewhere on the board
I2C1_SCL: U1.58 (PB6); also elsewhere on the board
I2C1_SDA: U1.59 (PB7); also elsewhere on the board
I2C2_SCL: U1.28 (PB10); also elsewhere on the board
I2C2_SDA: U1.29 (PB11); also elsewhere on the board
I2S1_CK: U1.21 (PA5); also elsewhere on the board
I2S1_SD: U1.23 (PA7); also elsewhere on the board
I2S1_WS: U1.20 (PA4); also elsewhere on the board
LED_BLUE: U1.33 (PB12); also elsewhere on the board
LED_GREEN: U1.35 (PB14); also elsewhere on the board
LED_RED: U1.36 (PB15); also elsewhere on the board
NRST: C9.1, SW6.1 (A), SW6.2 (B), U1.7 (NRST); also elsewhere on the board
RCC_MCO_1: U1.41 (PA8); also elsewhere on the board
SPI2_CS: U1.50 (PA15); also elsewhere on the board
SPI2_DC: U1.61 (PB8); also elsewhere on the board
SPI2_MISO: U1.10 (PC2); also elsewhere on the board
SPI2_MOSI: U1.9 (PC1); also elsewhere on the board
SPI2_RESET: U1.57 (PB5); also elsewhere on the board
SPI2_SCK: U1.34 (PB13); also elsewhere on the board
SYS_JTCK-SWCLK: U1.49 (PA14); also elsewhere on the board
SYS_JTMS-SWDIO: U1.46 (PA13); also elsewhere on the board
SYS_WKUP4: U1.2 (PC13); also elsewhere on the board
UART4_RX: U1.15 (PA1); also elsewhere on the board
UART4_TX: U1.14 (PA0); also elsewhere on the board
UART5_RX: U1.54 (PD2); also elsewhere on the board
UART5_TX: U1.53 (PC12); also elsewhere on the board
USART1_RX: U1.43 (PA10); also elsewhere on the board
USART1_TX: U1.42 (PA9); also elsewhere on the board
USART2_RX: U1.17 (PA3); also elsewhere on the board
USART2_TX: U1.16 (PA2); also elsewhere on the board
USART3_RX: U1.52 (PC11); also elsewhere on the board
USART3_TX: U1.51 (PC10); also elsewhere on the board
USART6_RX: U1.38 (PC7); also elsewhere on the board
USART6_TX: U1.37 (PC6); also elsewhere on the board
VBUS: C14.1, CN7.A4B9 (VBUS), CN7.B4A9 (VBUS), D10.2 (A2), J7.1, J7.2, U2.3 (VI)

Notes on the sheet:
USB App Note AN4879
Decoupling Capacitors 1x 100nF per VDD/VBAT See DS11853 Rev 9 page 155
Pull-up for USB_D+
Board powered by USB
Add ground protection for crystal in PCB
USB Device Mode Only
USB 2.0 impedance: 90 Ohms differential
Power Supply
ESD Protection
TODO: resettable fuses
VBUS from USB (nominally +5V); Min. 22μF input/output caps
VDDA Filtering
Note: No PC5
USB shield ground should NOT be connected to regular ground

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

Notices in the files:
stm-midi-poc1.kicad_pcb:
License: CC BY-SA 4.0
